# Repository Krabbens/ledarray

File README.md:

# Kolorowy wyświetlacz widmowy

## Spis Treści

- [Aplikacja](#flutter)
- [ESP PlatformIO](#esp-platformio)
- [PCB](#pcb)
- [Blender](#blender)
- [Przetwarzanie wstępne](#przetwarzanie-wstępne)

## Aplikacja do kontroli

1. Zainstaluj Flutter:

    - Pobierz Flutter SDK z https://flutter.dev/docs/get-started/install
    - Dodaj Flutter bin do PATH

2. Sprawdź instalację:

    ```bash
    flutter doctor
    ```

3. Uruchom projekt:

    ```bash
    cd /ścieżka/do/projektu
    flutter run
    ```

## ESP PlatformIO

1. Zainstaluj PlatformIO:

    - Pobierz PlatformIO IDE z https://platformio.org/install/ide?install=vscode

2. Skopiuj pliki z folderu esp/core_lib do odpowiadających folderów bibliotek espressif32 w domyślnej lokalizacji platformio

3. Uruchom projekt:

    - Otwórz PlatformIO IDE, załaduj projekt, użyj opcji "Build" i "Upload"

## PCB

1. Zainstaluj KiCad:

    - Pobierz KiCad z https://kicad.org/download/

2. Otwórz projekt:

    - Załaduj istniejący plik PCB w KiCad

## Blender

1. Zainstaluj Blender:

    - Pobierz Blender z https://www.blender.org/download/

2. Otwórz projekt:

    - Plik `cude.blend` jest głównym plikiem do renderowania animacji.
    - Plik `simul.blend` służy do symulacji animacji.

## Przetwarzanie wstępne

Zestaw skryptów służący do przetwarzania danych z blendera na format rozumiany przez program kontrolujący diody LED.

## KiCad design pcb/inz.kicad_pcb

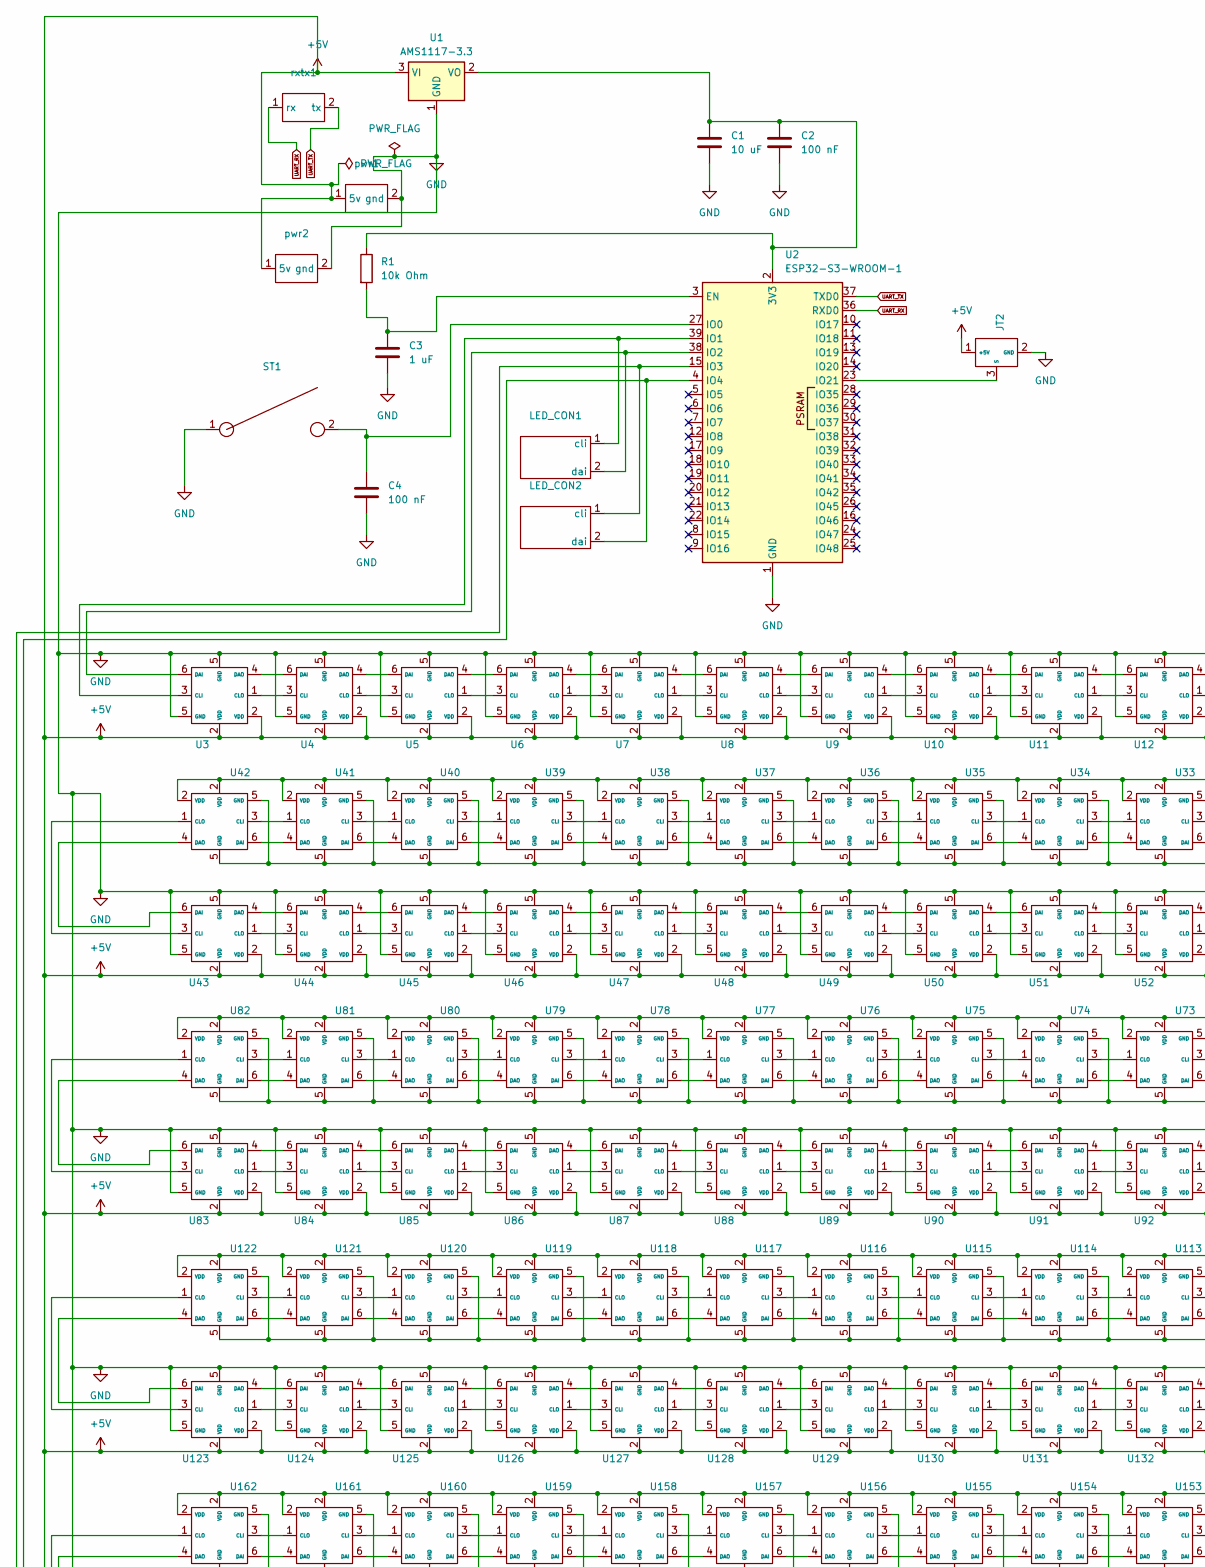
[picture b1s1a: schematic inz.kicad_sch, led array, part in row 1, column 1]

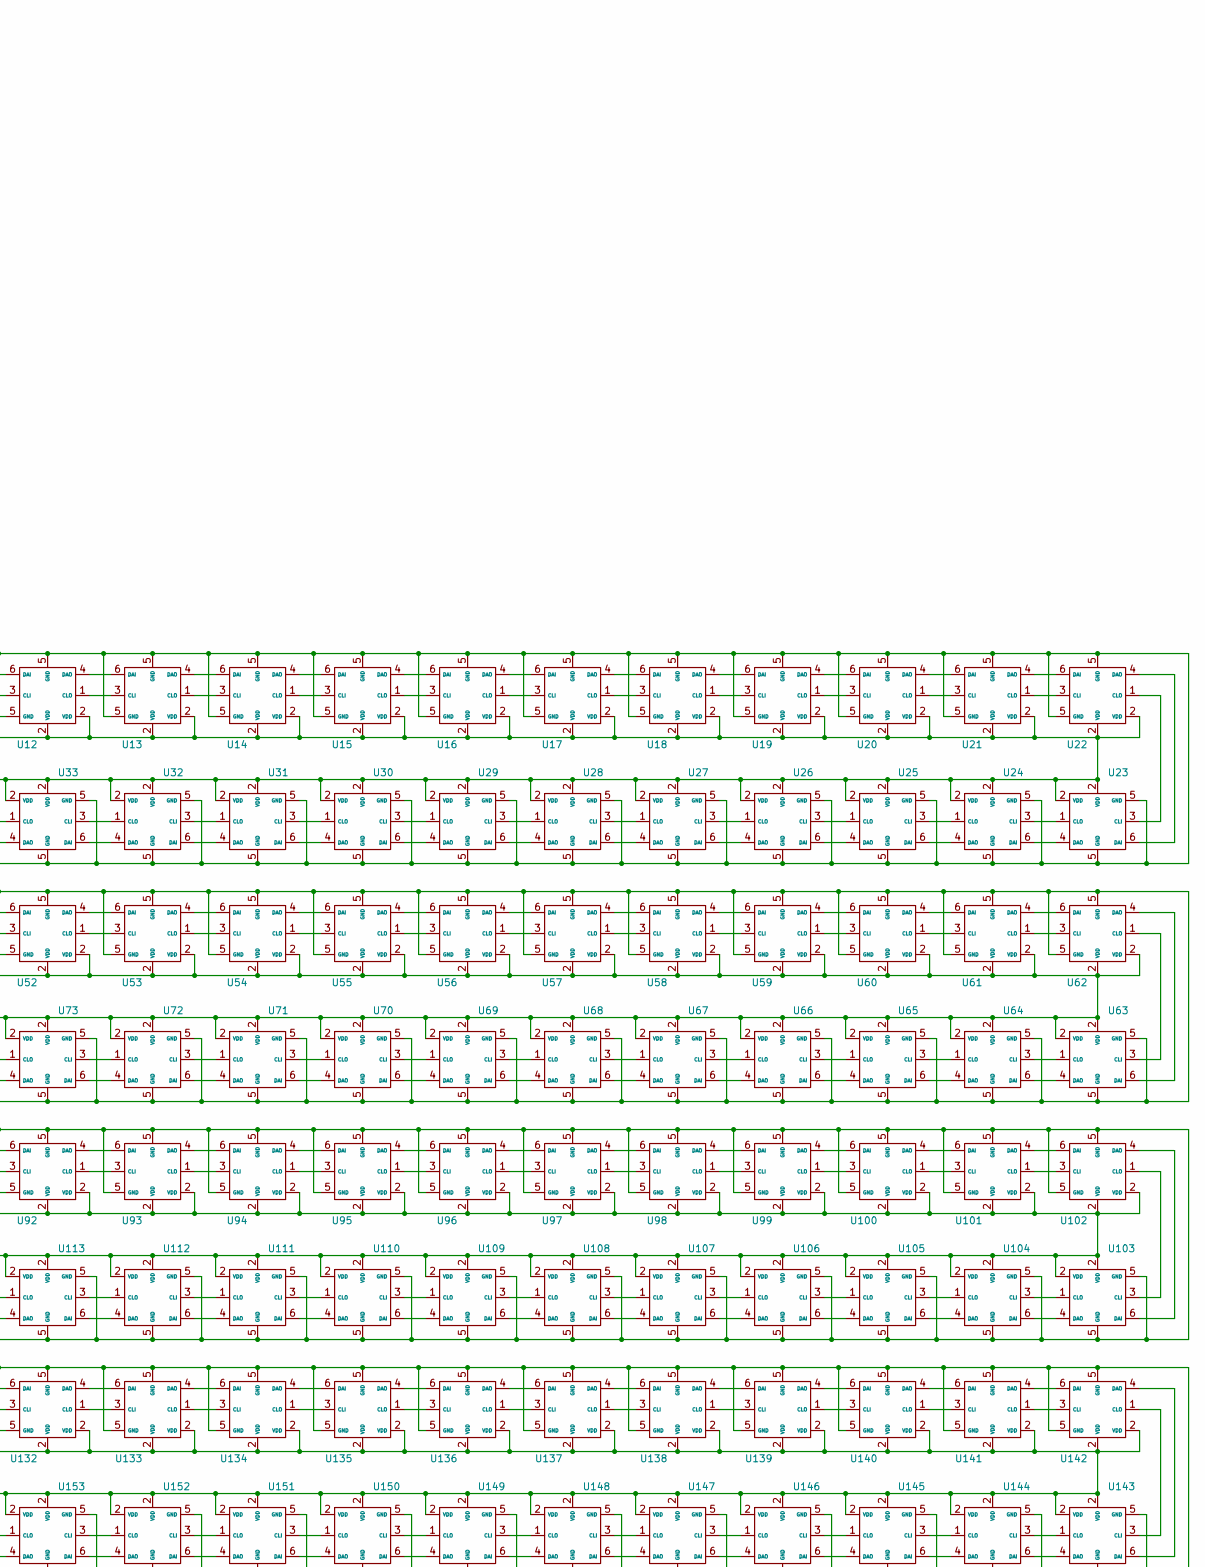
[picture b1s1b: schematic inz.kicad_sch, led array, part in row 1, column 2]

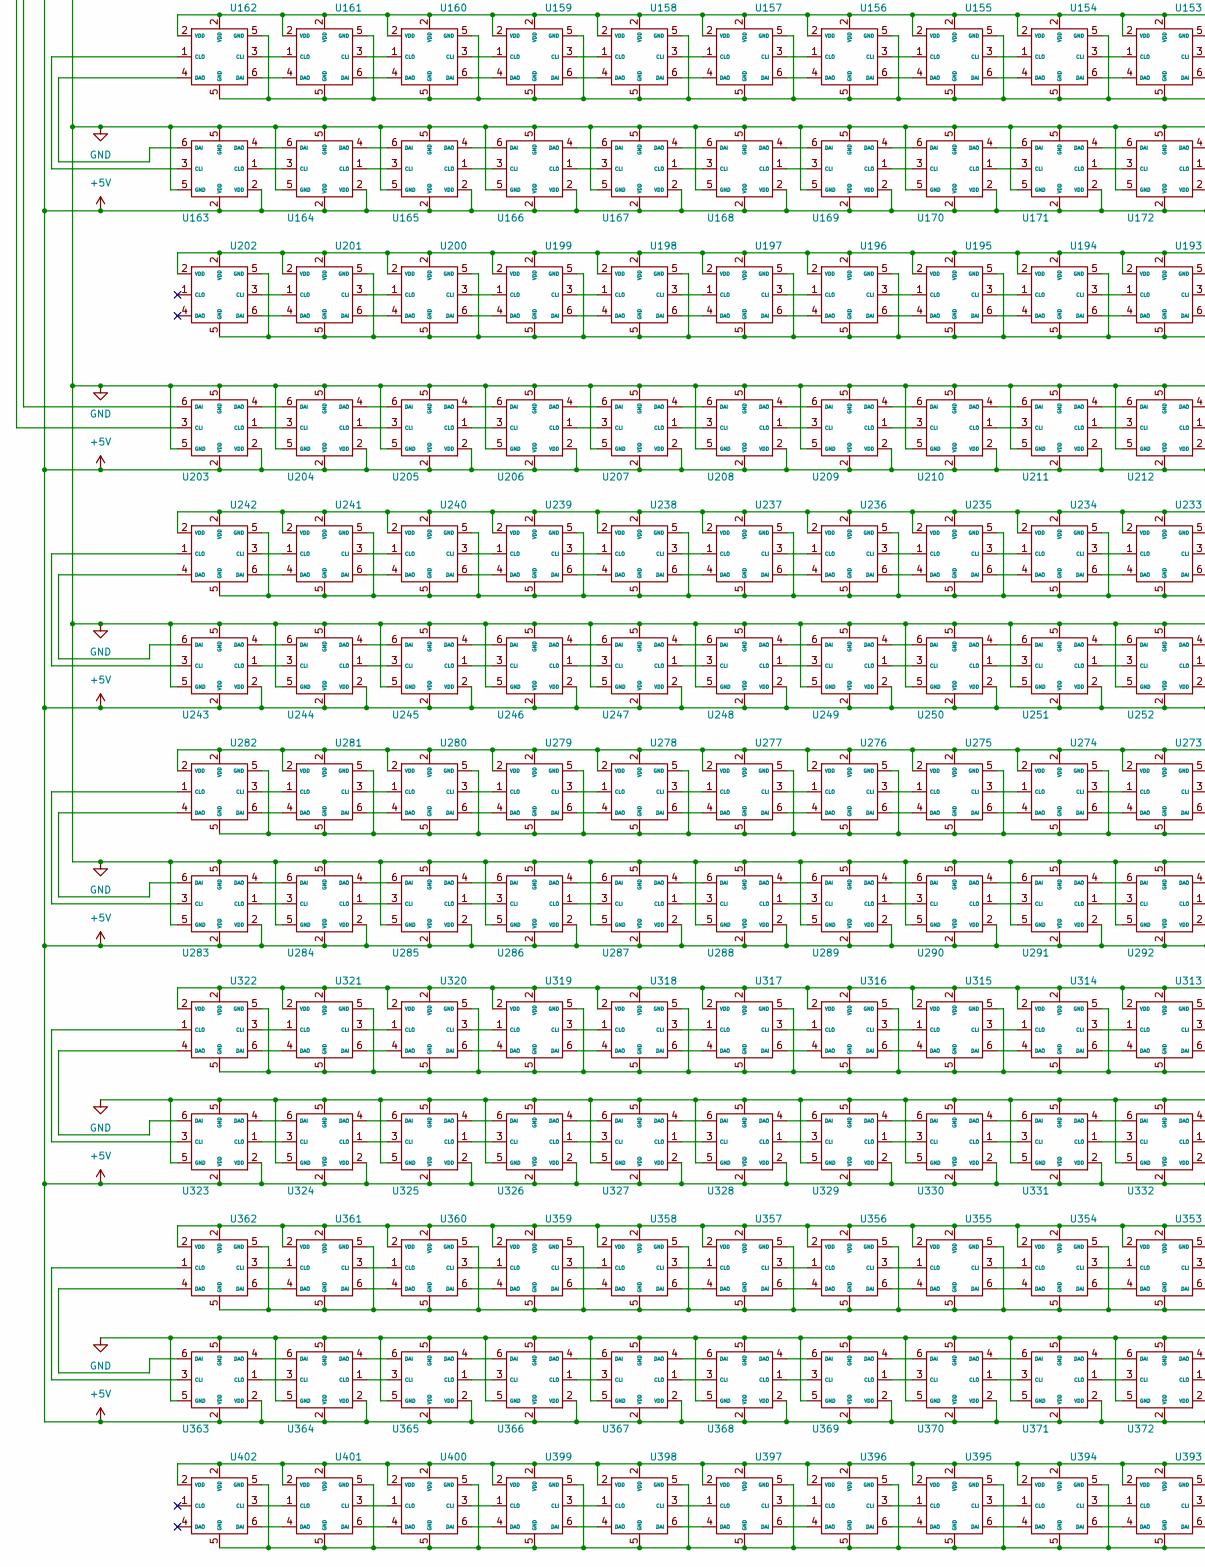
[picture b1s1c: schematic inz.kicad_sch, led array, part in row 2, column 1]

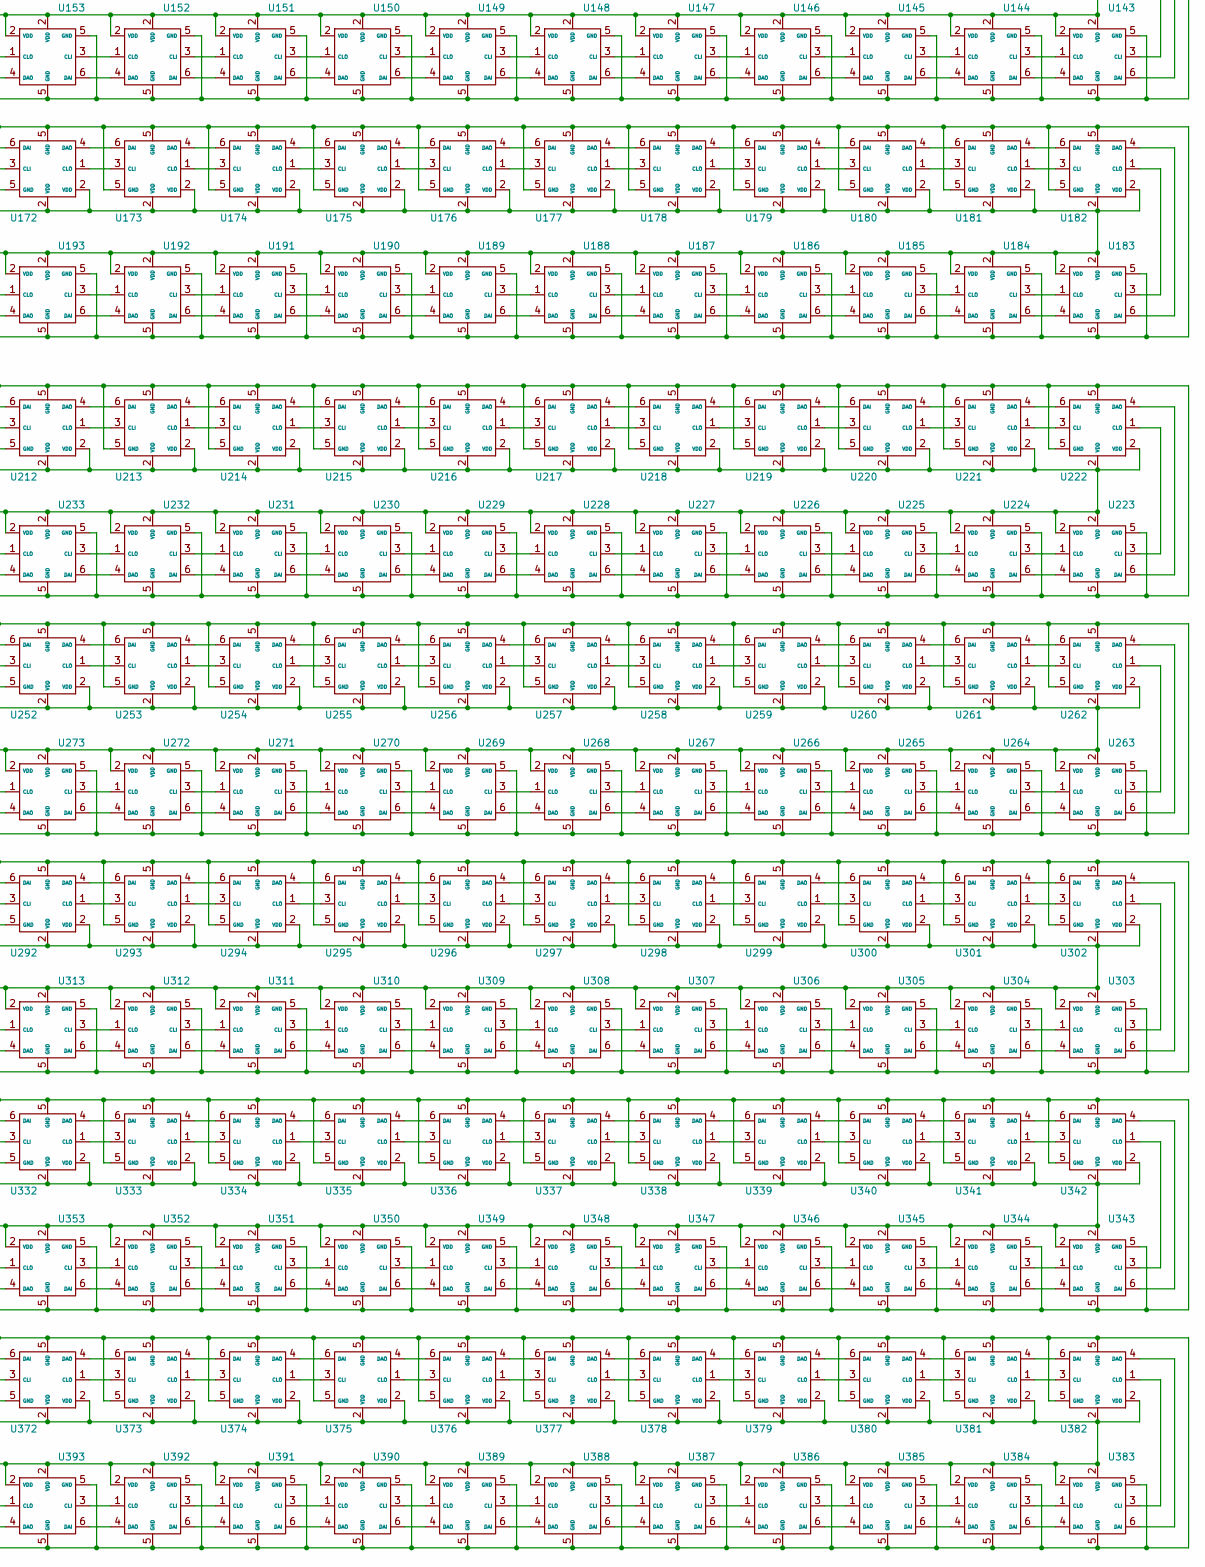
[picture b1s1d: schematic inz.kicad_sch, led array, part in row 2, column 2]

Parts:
C1: 10 uF; C_0603_1608Metric
C2, C4: 100 nF; C_0402_1005Metric
C3: 1 uF; C_0402_1005Metric
JT2: hall JT
LED_CON1, LED_CON2: led_con
R1: 10k Ohm; R_0402_1005Metric
ST1: ST-1185S
U1: AMS1117-3.3; SOT-223-3_TabPin2
U2: ESP32-S3-WROOM-1
U3, U4, U5, U6, U7, U8, U9, U10, U11, U12, U13, U14, U15, U16, U17, U18, U19, U20, U21, U22, U23, U24, U25, U26, U27, U28, U29, U30, U31, U32, U33, U34, U35, U36, U37, U38, U39, U40, U41, U42, U43, U44, U45, U46, U47, U48, U49, U50, U51, U52, U53, U54, U55, U56, U57, U58, U59, U60, U61, U62, U63, U64, U65, U66, U67, U68, U69, U70, U71, U72, U73, U74, U75, U76, U77, U78, U79, U80, U81, U82, U83, U84, U85, U86, U87, U88, U89, U90, U91, U92, U93, U94, U95, U96, U97, U98, U99, U100, U101, U102, U103, U104, U105, U106, U107, U108, U109, U110, U111, U112, U113, U114, U115, U116, U117, U118, U119, U120, U121, U122, U123, U124, U125, U126, U127, U128, U129, U130, U131, U132, U133, U134, U135, U136, U137, U138, U139, U140, U141, U142, U143, U144, U145, U146, U147, U148, U149, U150, U151, U152, U153, U154, U155, U156, U157, U158, U159, U160, U161, U162, U163, U164, U165, U166, U167, U168, U169, U170, U171, U172, U173, U174, U175, U176, U177, U178, U179, U180, U181, U182, U183, U184, U185, U186, U187, U188, U189, U190, U191, U192, U193, U194, U195, U196, U197, U198, U199, U200, U201, U202, U203, U204, U205, U206, U207, U208, U209, U210, U211, U212, U213, U214, U215, U216, U217, U218, U219, U220, U221, U222, U223, U224, U225, U226, U227, U228, U229, U230, U231, U232, U233, U234, U235, U236, U237, U238, U239, U240, U241, U242, U243, U244, U245, U246, U247, U248, U249, U250, U251, U252, U253, U254, U255, U256, U257, U258, U259, U260, U261, U262, U263, U264, U265, U266, U267, U268, U269, U270, U271, U272, U273, U274, U275, U276, U277, U278, U279, U280, U281, U282, U283, U284, U285, U286, U287, U288, U289, U290, U291, U292, U293, U294, U295, U296, U297, U298, U299, U300, U301, U302, U303, U304, U305, U306, U307, U308, U309, U310, U311, U312, U313, U314, U315, U316, U317, U318, U319, U320, U321, U322, U323, U324, U325, U326, U327, U328, U329, U330, U331, U332, U333, U334, U335, U336, U337, U338, U339, U340, U341, U342, U343, U344, U345, U346, U347, U348, U349, U350, U351, U352, U353, U354, U355, U356, U357, U358, U359, U360, U361, U362, U363, U364, U365, U366, U367, U368, U369, U370, U371, U372, U373, U374, U375, U376, U377, U378, U379, U380, U381, U382, U383, U384, U385, U386, U387, U388, U389, U390, U391, U392, U393, U394, U395, U396, U397, U398, U399, U400, U401, U402: APA102-2020-6A
pwr1, pwr2: 5vgnd
rxtx1: rxtx

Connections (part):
+5V: JT2.1 (+5V), U1.3 (VI), U3.2 (VDD), U4.2 (VDD), U5.2 (VDD), U6.2 (VDD), U7.2 (VDD), U8.2 (VDD), U9.2 (VDD), U10.2 (VDD), U11.2 (VDD), U12.2 (VDD), U13.2 (VDD), U14.2 (VDD), U15.2 (VDD), U16.2 (VDD), U17.2 (VDD), U18.2 (VDD), U19.2 (VDD), U20.2 (VDD), U21.2 (VDD), U22.2 (VDD), U23.2 (VDD), U24.2 (VDD), U25.2 (VDD), U26.2 (VDD), U27.2 (VDD), U28.2 (VDD), U29.2 (VDD), U30.2 (VDD), U31.2 (VDD), U32.2 (VDD), U33.2 (VDD), U34.2 (VDD), U35.2 (VDD), U36.2 (VDD), U37.2 (VDD), U38.2 (VDD), U39.2 (VDD), U40.2 (VDD), U41.2 (VDD), U42.2 (VDD), U43.2 (VDD), U44.2 (VDD), U45.2 (VDD), U46.2 (VDD), U47.2 (VDD), U48.2 (VDD), U49.2 (VDD), U50.2 (VDD), U51.2 (VDD), U52.2 (VDD), U53.2 (VDD), U54.2 (VDD), U55.2 (VDD), U56.2 (VDD), U57.2 (VDD), U58.2 (VDD), U59.2 (VDD), U60.2 (VDD), U61.2 (VDD), U62.2 (VDD), U63.2 (VDD), U64.2 (VDD), U65.2 (VDD), U66.2 (VDD), U67.2 (VDD), U68.2 (VDD), U69.2 (VDD), U70.2 (VDD), U71.2 (VDD), U72.2 (VDD), U73.2 (VDD), U74.2 (VDD), U75.2 (VDD), U76.2 (VDD), U77.2 (VDD), U78.2 (VDD), U79.2 (VDD), U80.2 (VDD)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
GND: C1.2, C2.2, C3.2, C4.2, JT2.2 (GND), ST1.1, U1.1 (GND), U2.1 (GND), U2.40 (GND), U2.41 (GND), U3.5 (GND), U4.5 (GND), U5.5 (GND), U6.5 (GND), U7.5 (GND), U8.5 (GND), U9.5 (GND), U10.5 (GND), U11.5 (GND), U12.5 (GND), U13.5 (GND), U14.5 (GND), U15.5 (GND), U16.5 (GND), U17.5 (GND), U18.5 (GND), U19.5 (GND), U20.5 (GND), U21.5 (GND), U22.5 (GND), U23.5 (GND), U24.5 (GND), U25.5 (GND), U26.5 (GND), U27.5 (GND), U28.5 (GND), U29.5 (GND), U30.5 (GND), U31.5 (GND), U32.5 (GND), U33.5 (GND), U34.5 (GND), U35.5 (GND), U36.5 (GND), U37.5 (GND), U38.5 (GND), U39.5 (GND), U40.5 (GND), U41.5 (GND), U42.5 (GND), U43.5 (GND), U44.5 (GND), U45.5 (GND), U46.5 (GND), U47.5 (GND), U48.5 (GND), U49.5 (GND), U50.5 (GND), U51.5 (GND), U52.5 (GND), U53.5 (GND), U54.5 (GND), U55.5 (GND), U56.5 (GND), U57.5 (GND), U58.5 (GND), U59.5 (GND), U60.5 (GND), U61.5 (GND), U62.5 (GND), U63.5 (GND), U64.5 (GND), U65.5 (GND), U66.5 (GND), U67.5 (GND), U68.5 (GND), U69.5 (GND), U70.5 (GND), U71.5 (GND), U72.5 (GND)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
unnamed: JT2.3 (S), U2.23 (IO21)
unnamed: LED_CON1.1 (cli), U2.39 (IO1), U3.3 (CLI)
unnamed: LED_CON1.2 (dai), U2.38 (IO2), U3.6 (DAI)
unnamed: LED_CON2.1 (cli), U2.15 (IO3), U203.3 (CLI)
unnamed: LED_CON2.2 (dai), U2.4 (IO4), U203.6 (DAI)
unnamed: C1.1, C2.1, R1.1, U1.2 (VO), U2.2 (3V3)
unnamed: C3.1, R1.2, U2.3 (EN)
unnamed: C4.1, ST1.2, U2.27 (IO0)
unnamed: U3.1 (CLO), U4.3 (CLI)
unnamed: U3.4 (DAO), U4.6 (DAI)
unnamed: U4.1 (CLO), U5.3 (CLI)
unnamed: U4.4 (DAO), U5.6 (DAI)
unnamed: U5.1 (CLO), U6.3 (CLI)
unnamed: U5.4 (DAO), U6.6 (DAI)
unnamed: U6.1 (CLO), U7.3 (CLI)
unnamed: U6.4 (DAO), U7.6 (DAI)
unnamed: U7.1 (CLO), U8.3 (CLI)
unnamed: U7.4 (DAO), U8.6 (DAI)
unnamed: U8.1 (CLO), U9.3 (CLI)
unnamed: U8.4 (DAO), U9.6 (DAI)
unnamed: U9.1 (CLO), U10.3 (CLI)
unnamed: U10.1 (CLO), U11.3 (CLI)
unnamed: U9.4 (DAO), U10.6 (DAI)
unnamed: U10.4 (DAO), U11.6 (DAI)
unnamed: U11.1 (CLO), U12.3 (CLI)
unnamed: U11.4 (DAO), U12.6 (DAI)
unnamed: U12.1 (CLO), U13.3 (CLI)
unnamed: U12.4 (DAO), U13.6 (DAI)
unnamed: U13.1 (CLO), U14.3 (CLI)
unnamed: U13.4 (DAO), U14.6 (DAI)
unnamed: U14.1 (CLO), U15.3 (CLI)
unnamed: U14.4 (DAO), U15.6 (DAI)
unnamed: U15.1 (CLO), U16.3 (CLI)
unnamed: U15.4 (DAO), U16.6 (DAI)
unnamed: U16.1 (CLO), U17.3 (CLI)
unnamed: U16.4 (DAO), U17.6 (DAI)
unnamed: U17.1 (CLO), U18.3 (CLI)
unnamed: U17.4 (DAO), U18.6 (DAI)
unnamed: U18.1 (CLO), U19.3 (CLI)
unnamed: U18.4 (DAO), U19.6 (DAI)
unnamed: U19.1 (CLO), U20.3 (CLI)
unnamed: U19.4 (DAO), U20.6 (DAI)
unnamed: U20.1 (CLO), U21.3 (CLI)
unnamed: U20.4 (DAO), U21.6 (DAI)
unnamed: U21.1 (CLO), U22.3 (CLI)
unnamed: U21.4 (DAO), U22.6 (DAI)
unnamed: U22.1 (CLO), U23.3 (CLI)
unnamed: U22.4 (DAO), U23.6 (DAI)
unnamed: U23.1 (CLO), U24.3 (CLI)
unnamed: U23.4 (DAO), U24.6 (DAI)
unnamed: U24.1 (CLO), U25.3 (CLI)
unnamed: U24.4 (DAO), U25.6 (DAI)
unnamed: U25.1 (CLO), U26.3 (CLI)
unnamed: U25.4 (DAO), U26.6 (DAI)
unnamed: U26.1 (CLO), U27.3 (CLI)
unnamed: U26.4 (DAO), U27.6 (DAI)
unnamed: U27.1 (CLO), U28.3 (CLI)
unnamed: U27.4 (DAO), U28.6 (DAI)
unnamed: U28.1 (CLO), U29.3 (CLI)
unnamed: U28.4 (DAO), U29.6 (DAI)
unnamed: U29.1 (CLO), U30.3 (CLI)
unnamed: U29.4 (DAO), U30.6 (DAI)
unnamed: U30.1 (CLO), U31.3 (CLI)
unnamed: U30.4 (DAO), U31.6 (DAI)
unnamed: U31.1 (CLO), U32.3 (CLI)
unnamed: U31.4 (DAO), U32.6 (DAI)
unnamed: U32.1 (CLO), U33.3 (CLI)
unnamed: U32.4 (DAO), U33.6 (DAI)
unnamed: U33.1 (CLO), U34.3 (CLI)
unnamed: U33.4 (DAO), U34.6 (DAI)
unnamed: U34.1 (CLO), U35.3 (CLI)
unnamed: U34.4 (DAO), U35.6 (DAI)
unnamed: U35.1 (CLO), U36.3 (CLI)
unnamed: U35.4 (DAO), U36.6 (DAI)
unnamed: U36.1 (CLO), U37.3 (CLI)
unnamed: U36.4 (DAO), U37.6 (DAI)
unnamed: U37.1 (CLO), U38.3 (CLI)
unnamed: U37.4 (DAO), U38.6 (DAI)
unnamed: U38.1 (CLO), U39.3 (CLI)
unnamed: U38.4 (DAO), U39.6 (DAI)
unnamed: U39.1 (CLO), U40.3 (CLI)
unnamed: U39.4 (DAO), U40.6 (DAI)
unnamed: U40.1 (CLO), U41.3 (CLI)
unnamed: U40.4 (DAO), U41.6 (DAI)
unnamed: U41.1 (CLO), U42.3 (CLI)
unnamed: U41.4 (DAO), U42.6 (DAI)
unnamed: U42.1 (CLO), U43.3 (CLI)
unnamed: U42.4 (DAO), U43.6 (DAI)
unnamed: U43.1 (CLO), U44.3 (CLI)
unnamed: U43.4 (DAO), U44.6 (DAI)
unnamed: U44.1 (CLO), U45.3 (CLI)
unnamed: U44.4 (DAO), U45.6 (DAI)
unnamed: U45.1 (CLO), U46.3 (CLI)
unnamed: U45.4 (DAO), U46.6 (DAI)
unnamed: U46.1 (CLO), U47.3 (CLI)
unnamed: U46.4 (DAO), U47.6 (DAI)
unnamed: U47.1 (CLO), U48.3 (CLI)
unnamed: U47.4 (DAO), U48.6 (DAI)
unnamed: U48.1 (CLO), U49.3 (CLI)
unnamed: U48.4 (DAO), U49.6 (DAI)
unnamed: U49.1 (CLO), U50.3 (CLI)
unnamed: U49.4 (DAO), U50.6 (DAI)
unnamed: U50.1 (CLO), U51.3 (CLI)
unnamed: U50.4 (DAO), U51.6 (DAI)
unnamed: U51.1 (CLO), U52.3 (CLI)
unnamed: U51.4 (DAO), U52.6 (DAI)
unnamed: U52.1 (CLO), U53.3 (CLI)
unnamed: U52.4 (DAO), U53.6 (DAI)
unnamed: U53.1 (CLO), U54.3 (CLI)
unnamed: U53.4 (DAO), U54.6 (DAI)
unnamed: U54.1 (CLO), U55.3 (CLI)
unnamed: U54.4 (DAO), U55.6 (DAI)
unnamed: U55.1 (CLO), U56.3 (CLI)
unnamed: U55.4 (DAO), U56.6 (DAI)
unnamed: U56.1 (CLO), U57.3 (CLI)
unnamed: U56.4 (DAO), U57.6 (DAI)
unnamed: U57.1 (CLO), U58.3 (CLI)
unnamed: U57.4 (DAO), U58.6 (DAI)
unnamed: U58.1 (CLO), U59.3 (CLI)
unnamed: U58.4 (DAO), U59.6 (DAI)
unnamed: U59.1 (CLO), U60.3 (CLI)
unnamed: U59.4 (DAO), U60.6 (DAI)
unnamed: U60.1 (CLO), U61.3 (CLI)
unnamed: U60.4 (DAO), U61.6 (DAI)
unnamed: U61.1 (CLO), U62.3 (CLI)
unnamed: U61.4 (DAO), U62.6 (DAI)
unnamed: U62.1 (CLO), U63.3 (CLI)
unnamed: U62.4 (DAO), U63.6 (DAI)
unnamed: U63.1 (CLO), U64.3 (CLI)
unnamed: U63.4 (DAO), U64.6 (DAI)
unnamed: U64.1 (CLO), U65.3 (CLI)
unnamed: U64.4 (DAO), U65.6 (DAI)
unnamed: U65.1 (CLO), U66.3 (CLI)
unnamed: U65.4 (DAO), U66.6 (DAI)
unnamed: U66.1 (CLO), U67.3 (CLI)
unnamed: U66.4 (DAO), U67.6 (DAI)
unnamed: U67.1 (CLO), U68.3 (CLI)
unnamed: U67.4 (DAO), U68.6 (DAI)
unnamed: U68.1 (CLO), U69.3 (CLI)
unnamed: U68.4 (DAO), U69.6 (DAI)
unnamed: U69.1 (CLO), U70.3 (CLI)
unnamed: U69.4 (DAO), U70.6 (DAI)
unnamed: U70.1 (CLO), U71.3 (CLI)
unnamed: U70.4 (DAO), U71.6 (DAI)
unnamed: U71.1 (CLO), U72.3 (CLI)
unnamed: U71.4 (DAO), U72.6 (DAI)
unnamed: U72.1 (CLO), U73.3 (CLI)
unnamed: U72.4 (DAO), U73.6 (DAI)
unnamed: U73.1 (CLO), U74.3 (CLI)
unnamed: U73.4 (DAO), U74.6 (DAI)
unnamed: U74.1 (CLO), U75.3 (CLI)
unnamed: U74.4 (DAO), U75.6 (DAI)
unnamed: U75.1 (CLO), U76.3 (CLI)
unnamed: U75.4 (DAO), U76.6 (DAI)
unnamed: U76.1 (CLO), U77.3 (CLI)
unnamed: U76.4 (DAO), U77.6 (DAI)
unnamed: U77.1 (CLO), U78.3 (CLI)
unnamed: U77.4 (DAO), U78.6 (DAI)
unnamed: U78.1 (CLO), U79.3 (CLI)
unnamed: U78.4 (DAO), U79.6 (DAI)
unnamed: U79.1 (CLO), U80.3 (CLI)
unnamed: U79.4 (DAO), U80.6 (DAI)
unnamed: U80.1 (CLO), U81.3 (CLI)
unnamed: U80.4 (DAO), U81.6 (DAI)
unnamed: U81.1 (CLO), U82.3 (CLI)
unnamed: U81.4 (DAO), U82.6 (DAI)
unnamed: U82.1 (CLO), U83.3 (CLI)
unnamed: U82.4 (DAO), U83.6 (DAI)
unnamed: U83.1 (CLO), U84.3 (CLI)
unnamed: U83.4 (DAO), U84.6 (DAI)
unnamed: U84.1 (CLO), U85.3 (CLI)
unnamed: U84.4 (DAO), U85.6 (DAI)
unnamed: U85.1 (CLO), U86.3 (CLI)
unnamed: U85.4 (DAO), U86.6 (DAI)
unnamed: U86.1 (CLO), U87.3 (CLI)
unnamed: U86.4 (DAO), U87.6 (DAI)
unnamed: U87.1 (CLO), U88.3 (CLI)
unnamed: U87.4 (DAO), U88.6 (DAI)
unnamed: U88.1 (CLO), U89.3 (CLI)
unnamed: U88.4 (DAO), U89.6 (DAI)
unnamed: U89.1 (CLO), U90.3 (CLI)
unnamed: U89.4 (DAO), U90.6 (DAI)
unnamed: U90.1 (CLO), U91.3 (CLI)
unnamed: U90.4 (DAO), U91.6 (DAI)
unnamed: U91.1 (CLO), U92.3 (CLI)
unnamed: U91.4 (DAO), U92.6 (DAI)
unnamed: U92.1 (CLO), U93.3 (CLI)
unnamed: U92.4 (DAO), U93.6 (DAI)
unnamed: U93.1 (CLO), U94.3 (CLI)
unnamed: U93.4 (DAO), U94.6 (DAI)
unnamed: U94.1 (CLO), U95.3 (CLI)
unnamed: U94.4 (DAO), U95.6 (DAI)
unnamed: U95.1 (CLO), U96.3 (CLI)
unnamed: U95.4 (DAO), U96.6 (DAI)
unnamed: U96.1 (CLO), U97.3 (CLI)
unnamed: U96.4 (DAO), U97.6 (DAI)
unnamed: U97.1 (CLO), U98.3 (CLI)
unnamed: U97.4 (DAO), U98.6 (DAI)
unnamed: U98.1 (CLO), U99.3 (CLI)
unnamed: U98.4 (DAO), U99.6 (DAI)
unnamed: U99.1 (CLO), U100.3 (CLI)
unnamed: U100.1 (CLO), U101.3 (CLI)
unnamed: U99.4 (DAO), U100.6 (DAI)
unnamed: U100.4 (DAO), U101.6 (DAI)
unnamed: U101.1 (CLO), U102.3 (CLI)
unnamed: U101.4 (DAO), U102.6 (DAI)
unnamed: U102.1 (CLO), U103.3 (CLI)
unnamed: U102.4 (DAO), U103.6 (DAI)
unnamed: U103.1 (CLO), U104.3 (CLI)
unnamed: U103.4 (DAO), U104.6 (DAI)
unnamed: U104.1 (CLO), U105.3 (CLI)
unnamed: U104.4 (DAO), U105.6 (DAI)
unnamed: U105.1 (CLO), U106.3 (CLI)
unnamed: U105.4 (DAO), U106.6 (DAI)
unnamed: U106.1 (CLO), U107.3 (CLI)
unnamed: U106.4 (DAO), U107.6 (DAI)
unnamed: U107.1 (CLO), U108.3 (CLI)
unnamed: U107.4 (DAO), U108.6 (DAI)
unnamed: U108.1 (CLO), U109.3 (CLI)
unnamed: U108.4 (DAO), U109.6 (DAI)
unnamed: U109.1 (CLO), U110.3 (CLI)
unnamed: U109.4 (DAO), U110.6 (DAI)
unnamed: U110.1 (CLO), U111.3 (CLI)
unnamed: U110.4 (DAO), U111.6 (DAI)
unnamed: U111.1 (CLO), U112.3 (CLI)
unnamed: U111.4 (DAO), U112.6 (DAI)
unnamed: U112.1 (CLO), U113.3 (CLI)
unnamed: U112.4 (DAO), U113.6 (DAI)
unnamed: U113.1 (CLO), U114.3 (CLI)
unnamed: U113.4 (DAO), U114.6 (DAI)
unnamed: U114.1 (CLO), U115.3 (CLI)
unnamed: U114.4 (DAO), U115.6 (DAI)
unnamed: U115.1 (CLO), U116.3 (CLI)
unnamed: U115.4 (DAO), U116.6 (DAI)
unnamed: U116.1 (CLO), U117.3 (CLI)
unnamed: U116.4 (DAO), U117.6 (DAI)
unnamed: U117.1 (CLO), U118.3 (CLI)
unnamed: U117.4 (DAO), U118.6 (DAI)
unnamed: U118.1 (CLO), U119.3 (CLI)
unnamed: U118.4 (DAO), U119.6 (DAI)
unnamed: U119.1 (CLO), U120.3 (CLI)
unnamed: U119.4 (DAO), U120.6 (DAI)
unnamed: U120.1 (CLO), U121.3 (CLI)
unnamed: U120.4 (DAO), U121.6 (DAI)
unnamed: U121.1 (CLO), U122.3 (CLI)
unnamed: U121.4 (DAO), U122.6 (DAI)
unnamed: U122.1 (CLO), U123.3 (CLI)
unnamed: U122.4 (DAO), U123.6 (DAI)
unnamed: U123.1 (CLO), U124.3 (CLI)
unnamed: U123.4 (DAO), U124.6 (DAI)
unnamed: U124.1 (CLO), U125.3 (CLI)
unnamed: U124.4 (DAO), U125.6 (DAI)
unnamed: U125.1 (CLO), U126.3 (CLI)
unnamed: U125.4 (DAO), U126.6 (DAI)
unnamed: U126.1 (CLO), U127.3 (CLI)
unnamed: U126.4 (DAO), U127.6 (DAI)
unnamed: U127.1 (CLO), U128.3 (CLI)
unnamed: U127.4 (DAO), U128.6 (DAI)
unnamed: U128.1 (CLO), U129.3 (CLI)
unnamed: U128.4 (DAO), U129.6 (DAI)
unnamed: U129.1 (CLO), U130.3 (CLI)
unnamed: U129.4 (DAO), U130.6 (DAI)
unnamed: U130.1 (CLO), U131.3 (CLI)
unnamed: U130.4 (DAO), U131.6 (DAI)
unnamed: U131.1 (CLO), U132.3 (CLI)
unnamed: U131.4 (DAO), U132.6 (DAI)
unnamed: U132.1 (CLO), U133.3 (CLI)
unnamed: U132.4 (DAO), U133.6 (DAI)
unnamed: U133.1 (CLO), U134.3 (CLI)
unnamed: U133.4 (DAO), U134.6 (DAI)
unnamed: U134.1 (CLO), U135.3 (CLI)
unnamed: U134.4 (DAO), U135.6 (DAI)
unnamed: U135.1 (CLO), U136.3 (CLI)
unnamed: U135.4 (DAO), U136.6 (DAI)
unnamed: U136.1 (CLO), U137.3 (CLI)
unnamed: U136.4 (DAO), U137.6 (DAI)
unnamed: U137.1 (CLO), U138.3 (CLI)
unnamed: U137.4 (DAO), U138.6 (DAI)
unnamed: U138.1 (CLO), U139.3 (CLI)
unnamed: U138.4 (DAO), U139.6 (DAI)
unnamed: U139.1 (CLO), U140.3 (CLI)
unnamed: U139.4 (DAO), U140.6 (DAI)
unnamed: U140.1 (CLO), U141.3 (CLI)
unnamed: U140.4 (DAO), U141.6 (DAI)
unnamed: U141.1 (CLO), U142.3 (CLI)
unnamed: U141.4 (DAO), U142.6 (DAI)
unnamed: U142.1 (CLO), U143.3 (CLI)
unnamed: U142.4 (DAO), U143.6 (DAI)
unnamed: U143.1 (CLO), U144.3 (CLI)
unnamed: U143.4 (DAO), U144.6 (DAI)
unnamed: U144.1 (CLO), U145.3 (CLI)
unnamed: U144.4 (DAO), U145.6 (DAI)
unnamed: U145.1 (CLO), U146.3 (CLI)
unnamed: U145.4 (DAO), U146.6 (DAI)
unnamed: U146.1 (CLO), U147.3 (CLI)
unnamed: U146.4 (DAO), U147.6 (DAI)
unnamed: U147.1 (CLO), U148.3 (CLI)
unnamed: U147.4 (DAO), U148.6 (DAI)
unnamed: U148.1 (CLO), U149.3 (CLI)
unnamed: U148.4 (DAO), U149.6 (DAI)
unnamed: U149.1 (CLO), U150.3 (CLI)
unnamed: U149.4 (DAO), U150.6 (DAI)
unnamed: U150.1 (CLO), U151.3 (CLI)
unnamed: U150.4 (DAO), U151.6 (DAI)
unnamed: U151.1 (CLO), U152.3 (CLI)
unnamed: U151.4 (DAO), U152.6 (DAI)
unnamed: U152.1 (CLO), U153.3 (CLI)
unnamed: U152.4 (DAO), U153.6 (DAI)
unnamed: U153.1 (CLO), U154.3 (CLI)
unnamed: U153.4 (DAO), U154.6 (DAI)
unnamed: U154.1 (CLO), U155.3 (CLI)
unnamed: U154.4 (DAO), U155.6 (DAI)
unnamed: U155.1 (CLO), U156.3 (CLI)
unnamed: U155.4 (DAO), U156.6 (DAI)
unnamed: U156.1 (CLO), U157.3 (CLI)
unnamed: U156.4 (DAO), U157.6 (DAI)
unnamed: U157.1 (CLO), U158.3 (CLI)
unnamed: U157.4 (DAO), U158.6 (DAI)
unnamed: U158.1 (CLO), U159.3 (CLI)
unnamed: U158.4 (DAO), U159.6 (DAI)
unnamed: U159.1 (CLO), U160.3 (CLI)
unnamed: U159.4 (DAO), U160.6 (DAI)
unnamed: U160.1 (CLO), U161.3 (CLI)
unnamed: U160.4 (DAO), U161.6 (DAI)
unnamed: U161.1 (CLO), U162.3 (CLI)
unnamed: U161.4 (DAO), U162.6 (DAI)
unnamed: U162.1 (CLO), U163.3 (CLI)
unnamed: U162.4 (DAO), U163.6 (DAI)
unnamed: U163.1 (CLO), U164.3 (CLI)
unnamed: U163.4 (DAO), U164.6 (DAI)
unnamed: U164.1 (CLO), U165.3 (CLI)
unnamed: U164.4 (DAO), U165.6 (DAI)
unnamed: U165.1 (CLO), U166.3 (CLI)
unnamed: U165.4 (DAO), U166.6 (DAI)
unnamed: U166.1 (CLO), U167.3 (CLI)
unnamed: U166.4 (DAO), U167.6 (DAI)
unnamed: U167.1 (CLO), U168.3 (CLI)
unnamed: U167.4 (DAO), U168.6 (DAI)
unnamed: U168.1 (CLO), U169.3 (CLI)
unnamed: U168.4 (DAO), U169.6 (DAI)
unnamed: U169.1 (CLO), U170.3 (CLI)
unnamed: U169.4 (DAO), U170.6 (DAI)
unnamed: U170.1 (CLO), U171.3 (CLI)
unnamed: U170.4 (DAO), U171.6 (DAI)
unnamed: U171.1 (CLO), U172.3 (CLI)
unnamed: U171.4 (DAO), U172.6 (DAI)
unnamed: U172.1 (CLO), U173.3 (CLI)
unnamed: U172.4 (DAO), U173.6 (DAI)
unnamed: U173.1 (CLO), U174.3 (CLI)
unnamed: U173.4 (DAO), U174.6 (DAI)
unnamed: U174.1 (CLO), U175.3 (CLI)
unnamed: U174.4 (DAO), U175.6 (DAI)
unnamed: U175.1 (CLO), U176.3 (CLI)
unnamed: U175.4 (DAO), U176.6 (DAI)
unnamed: U176.1 (CLO), U177.3 (CLI)
unnamed: U176.4 (DAO), U177.6 (DAI)
unnamed: U177.1 (CLO), U178.3 (CLI)
unnamed: U177.4 (DAO), U178.6 (DAI)
unnamed: U178.1 (CLO), U179.3 (CLI)
unnamed: U178.4 (DAO), U179.6 (DAI)
unnamed: U179.1 (CLO), U180.3 (CLI)
unnamed: U179.4 (DAO), U180.6 (DAI)
unnamed: U180.1 (CLO), U181.3 (CLI)
unnamed: U180.4 (DAO), U181.6 (DAI)
unnamed: U181.1 (CLO), U182.3 (CLI)
unnamed: U181.4 (DAO), U182.6 (DAI)
unnamed: U182.1 (CLO), U183.3 (CLI)
unnamed: U182.4 (DAO), U183.6 (DAI)
unnamed: U183.1 (CLO), U184.3 (CLI)
unnamed: U183.4 (DAO), U184.6 (DAI)
unnamed: U184.1 (CLO), U185.3 (CLI)
unnamed: U184.4 (DAO), U185.6 (DAI)
unnamed: U185.1 (CLO), U186.3 (CLI)
unnamed: U185.4 (DAO), U186.6 (DAI)
unnamed: U186.1 (CLO), U187.3 (CLI)
unnamed: U186.4 (DAO), U187.6 (DAI)
unnamed: U187.1 (CLO), U188.3 (CLI)
unnamed: U187.4 (DAO), U188.6 (DAI)
unnamed: U188.1 (CLO), U189.3 (CLI)
unnamed: U188.4 (DAO), U189.6 (DAI)
unnamed: U189.1 (CLO), U190.3 (CLI)
unnamed: U189.4 (DAO), U190.6 (DAI)
unnamed: U190.1 (CLO), U191.3 (CLI)
unnamed: U190.4 (DAO), U191.6 (DAI)
unnamed: U191.1 (CLO), U192.3 (CLI)
unnamed: U191.4 (DAO), U192.6 (DAI)
unnamed: U192.1 (CLO), U193.3 (CLI)
unnamed: U192.4 (DAO), U193.6 (DAI)
unnamed: U193.1 (CLO), U194.3 (CLI)
unnamed: U193.4 (DAO), U194.6 (DAI)
unnamed: U194.1 (CLO), U195.3 (CLI)
unnamed: U194.4 (DAO), U195.6 (DAI)
unnamed: U195.1 (CLO), U196.3 (CLI)
unnamed: U195.4 (DAO), U196.6 (DAI)
unnamed: U196.1 (CLO), U197.3 (CLI)
unnamed: U196.4 (DAO), U197.6 (DAI)
unnamed: U197.1 (CLO), U198.3 (CLI)
unnamed: U197.4 (DAO), U198.6 (DAI)
unnamed: U198.1 (CLO), U199.3 (CLI)
unnamed: U198.4 (DAO), U199.6 (DAI)
unnamed: U199.1 (CLO), U200.3 (CLI)
unnamed: U199.4 (DAO), U200.6 (DAI)
unnamed: U200.1 (CLO), U201.3 (CLI)
unnamed: U200.4 (DAO), U201.6 (DAI)
unnamed: U201.1 (CLO), U202.3 (CLI)
unnamed: U201.4 (DAO), U202.6 (DAI)
unnamed: U203.1 (CLO), U204.3 (CLI)
unnamed: U203.4 (DAO), U204.6 (DAI)
unnamed: U204.1 (CLO), U205.3 (CLI)
unnamed: U204.4 (DAO), U205.6 (DAI)
unnamed: U205.1 (CLO), U206.3 (CLI)
unnamed: U205.4 (DAO), U206.6 (DAI)
unnamed: U206.1 (CLO), U207.3 (CLI)
unnamed: U206.4 (DAO), U207.6 (DAI)
unnamed: U207.1 (CLO), U208.3 (CLI)
unnamed: U207.4 (DAO), U208.6 (DAI)
unnamed: U208.1 (CLO), U209.3 (CLI)
unnamed: U208.4 (DAO), U209.6 (DAI)
unnamed: U209.1 (CLO), U210.3 (CLI)
unnamed: U209.4 (DAO), U210.6 (DAI)
unnamed: U210.1 (CLO), U211.3 (CLI)
unnamed: U210.4 (DAO), U211.6 (DAI)
unnamed: U211.1 (CLO), U212.3 (CLI)
unnamed: U211.4 (DAO), U212.6 (DAI)
unnamed: U212.1 (CLO), U213.3 (CLI)
unnamed: U212.4 (DAO), U213.6 (DAI)
unnamed: U213.1 (CLO), U214.3 (CLI)
unnamed: U213.4 (DAO), U214.6 (DAI)
unnamed: U214.1 (CLO), U215.3 (CLI)
unnamed: U214.4 (DAO), U215.6 (DAI)
unnamed: U215.1 (CLO), U216.3 (CLI)
unnamed: U215.4 (DAO), U216.6 (DAI)
unnamed: U216.1 (CLO), U217.3 (CLI)
unnamed: U216.4 (DAO), U217.6 (DAI)
unnamed: U217.1 (CLO), U218.3 (CLI)
unnamed: U217.4 (DAO), U218.6 (DAI)
unnamed: U218.1 (CLO), U219.3 (CLI)
unnamed: U218.4 (DAO), U219.6 (DAI)
unnamed: U219.1 (CLO), U220.3 (CLI)
unnamed: U219.4 (DAO), U220.6 (DAI)
unnamed: U220.1 (CLO), U221.3 (CLI)
unnamed: U220.4 (DAO), U221.6 (DAI)
unnamed: U221.1 (CLO), U222.3 (CLI)
unnamed: U221.4 (DAO), U222.6 (DAI)
unnamed: U222.1 (CLO), U223.3 (CLI)
unnamed: U222.4 (DAO), U223.6 (DAI)
unnamed: U223.1 (CLO), U224.3 (CLI)
unnamed: U223.4 (DAO), U224.6 (DAI)
unnamed: U224.1 (CLO), U225.3 (CLI)
unnamed: U224.4 (DAO), U225.6 (DAI)
unnamed: U225.1 (CLO), U226.3 (CLI)
unnamed: U225.4 (DAO), U226.6 (DAI)
unnamed: U226.1 (CLO), U227.3 (CLI)
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
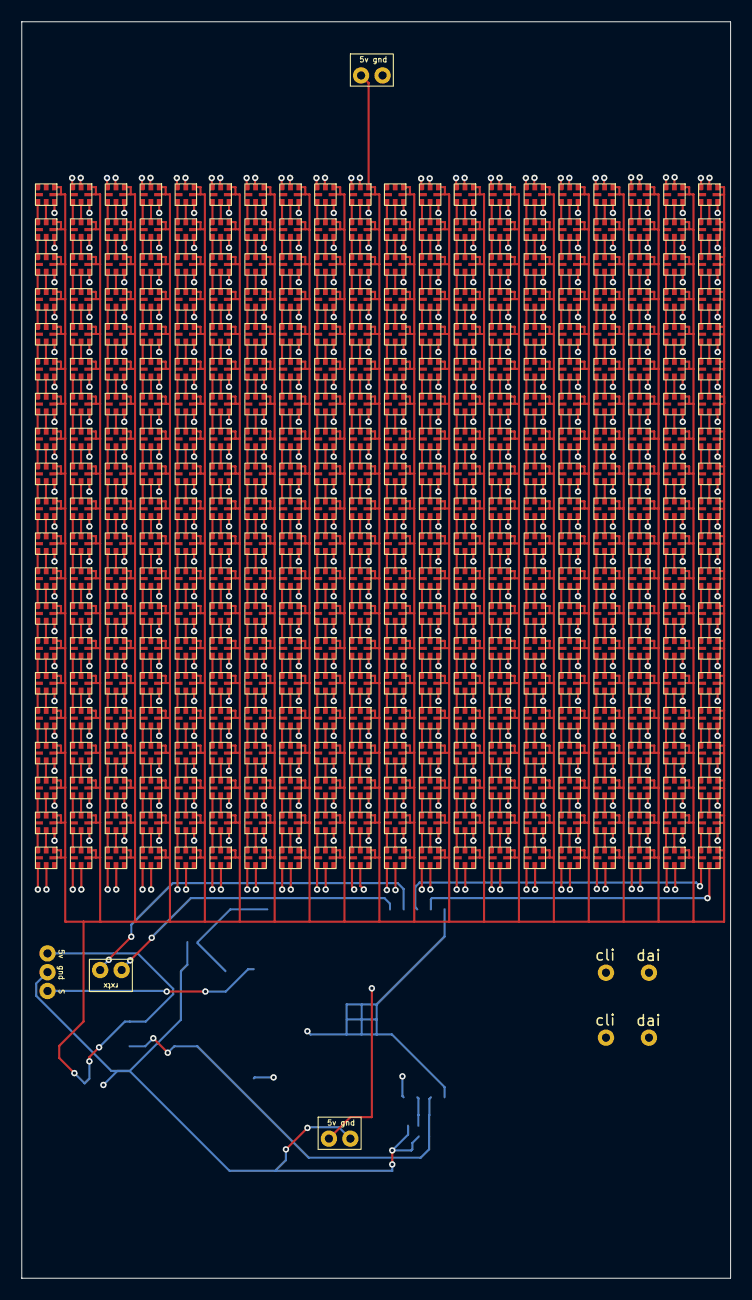
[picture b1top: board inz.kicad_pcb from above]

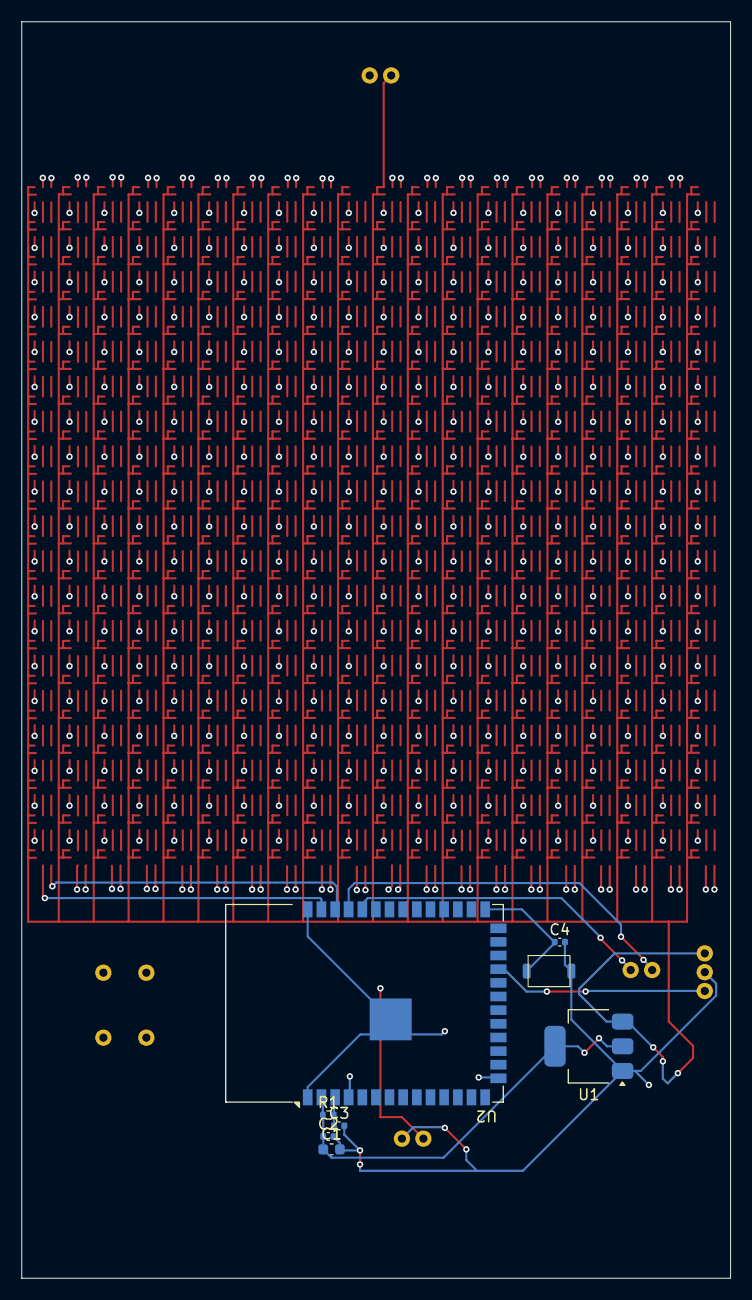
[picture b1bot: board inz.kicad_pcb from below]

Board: 4 copper layers, 66.0 x 117.0 mm, 414 parts (8 on the bottom side), 808 nets.
